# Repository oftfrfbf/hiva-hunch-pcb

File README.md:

# H.I.V.A Hunch PCB v2

The H.I.V.A Hunch PCB v2 is a medical device designed to monitor and restrict the presence of gas bubbles suspended in fluid passing through PVC tubing.

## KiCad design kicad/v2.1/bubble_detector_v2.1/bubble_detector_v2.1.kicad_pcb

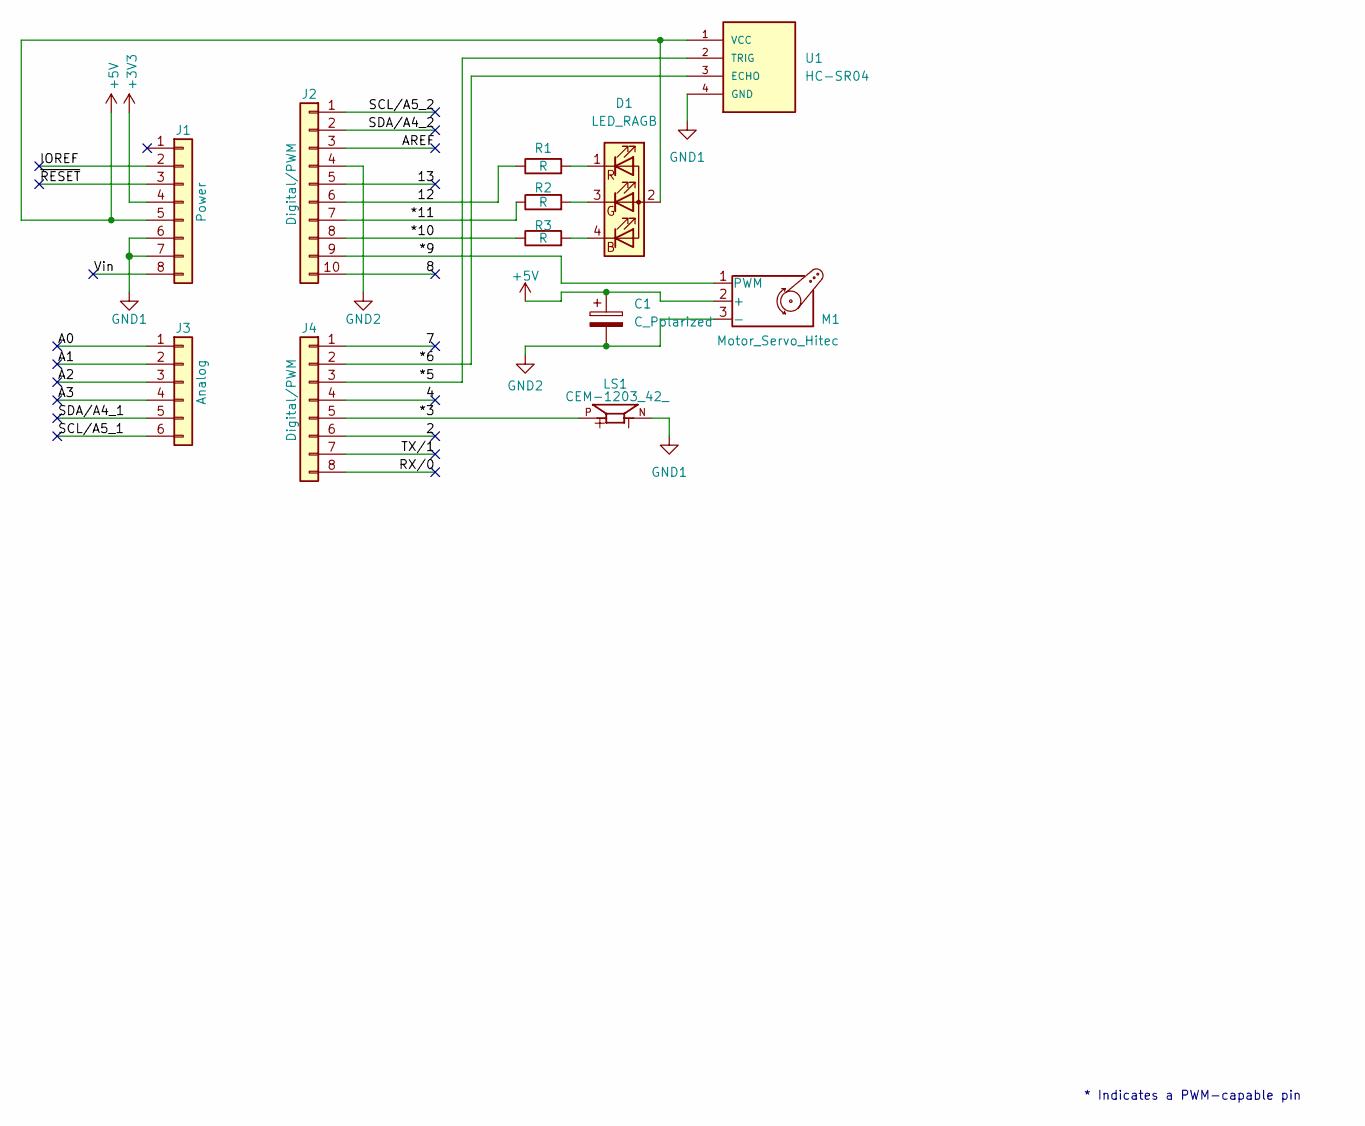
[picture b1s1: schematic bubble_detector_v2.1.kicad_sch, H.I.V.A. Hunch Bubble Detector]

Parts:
C1: C_Polarized; CP_Radial_D5.0mm_P2.50mm
D1: LED_RAGB; LED_D5.0mm-4_RGB
J1: Power; PinSocket_1x08_P2.54mm_Vertical
J2: Digital/PWM; PinSocket_1x10_P2.54mm_Vertical
J3: Analog; PinSocket_1x06_P2.54mm_Vertical
J4: Digital/PWM; PinSocket_1x08_P2.54mm_Vertical
LS1: CEM-1203_42_
M1: Motor_Servo_Hitec; PinHeader_1x03_P2.54mm_Vertical
R1, R2, R3: R; R_Axial_DIN0309_L9.0mm_D3.2mm_P12.70mm_Horizontal
U1: HC-SR04; XCVR_HC-SR04

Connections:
+3V3: J1.4
+5V: C1.1, D1.2 (A), J1.5, M1.2 (+), U1.1 (VCC)
/2: J4.6
/4: J4.4
/7: J4.1
/8: J2.10
/12: J2.6, R1.1
/13: J2.5
/*3: J4.5, LS1.P
/*5: J4.3, U1.2 (TRIG)
/*6: J4.2, U1.3 (ECHO)
/*9: J2.9, M1.1 (PWM)
/*10: J2.8, R3.1
/*11: J2.7, R2.1
/A0: J3.1
/A1: J3.2
/A2: J3.3
/A3: J3.4
/AREF: J2.3
/IOREF: J1.2
/RX/0: J4.8
/SCL/A5_1: J3.6
/SCL/A5_2: J2.1
/SDA/A4_1: J3.5
/SDA/A4_2: J2.2
/TX/1: J4.7
/Vin: J1.8
/~RESET: J1.3
GND1: J1.6, J1.7, LS1.N, U1.4 (GND)
GND2: C1.2, J2.4, M1.3 (-)
unnamed: D1.4 (BK), R3.2
unnamed: D1.3 (GK), R2.2
unnamed: D1.1 (RK), R1.2

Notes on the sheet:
* Indicates a PWM-capable pin

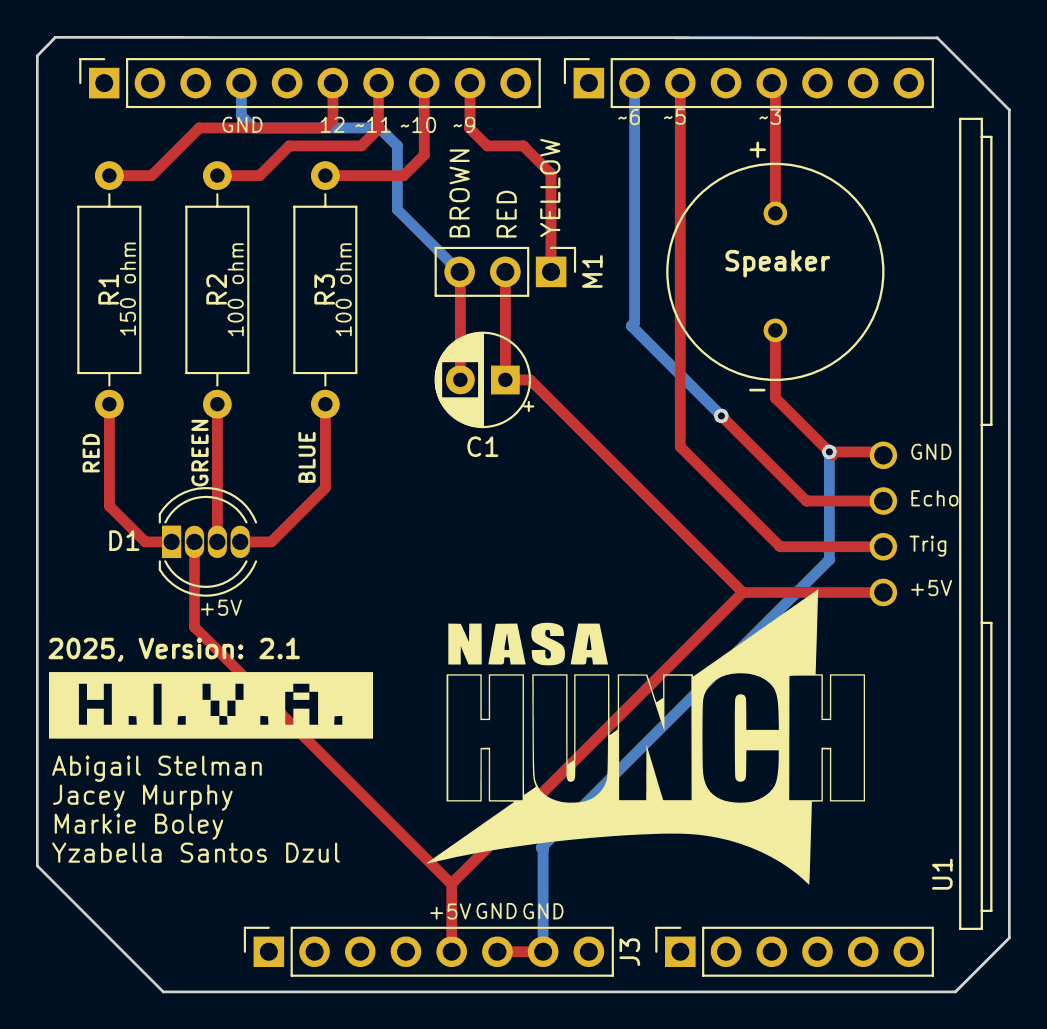
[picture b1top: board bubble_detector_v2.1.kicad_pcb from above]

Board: 2 copper layers, 54.0 x 53.0 mm, 12 parts (0 on the bottom side), 13 nets.

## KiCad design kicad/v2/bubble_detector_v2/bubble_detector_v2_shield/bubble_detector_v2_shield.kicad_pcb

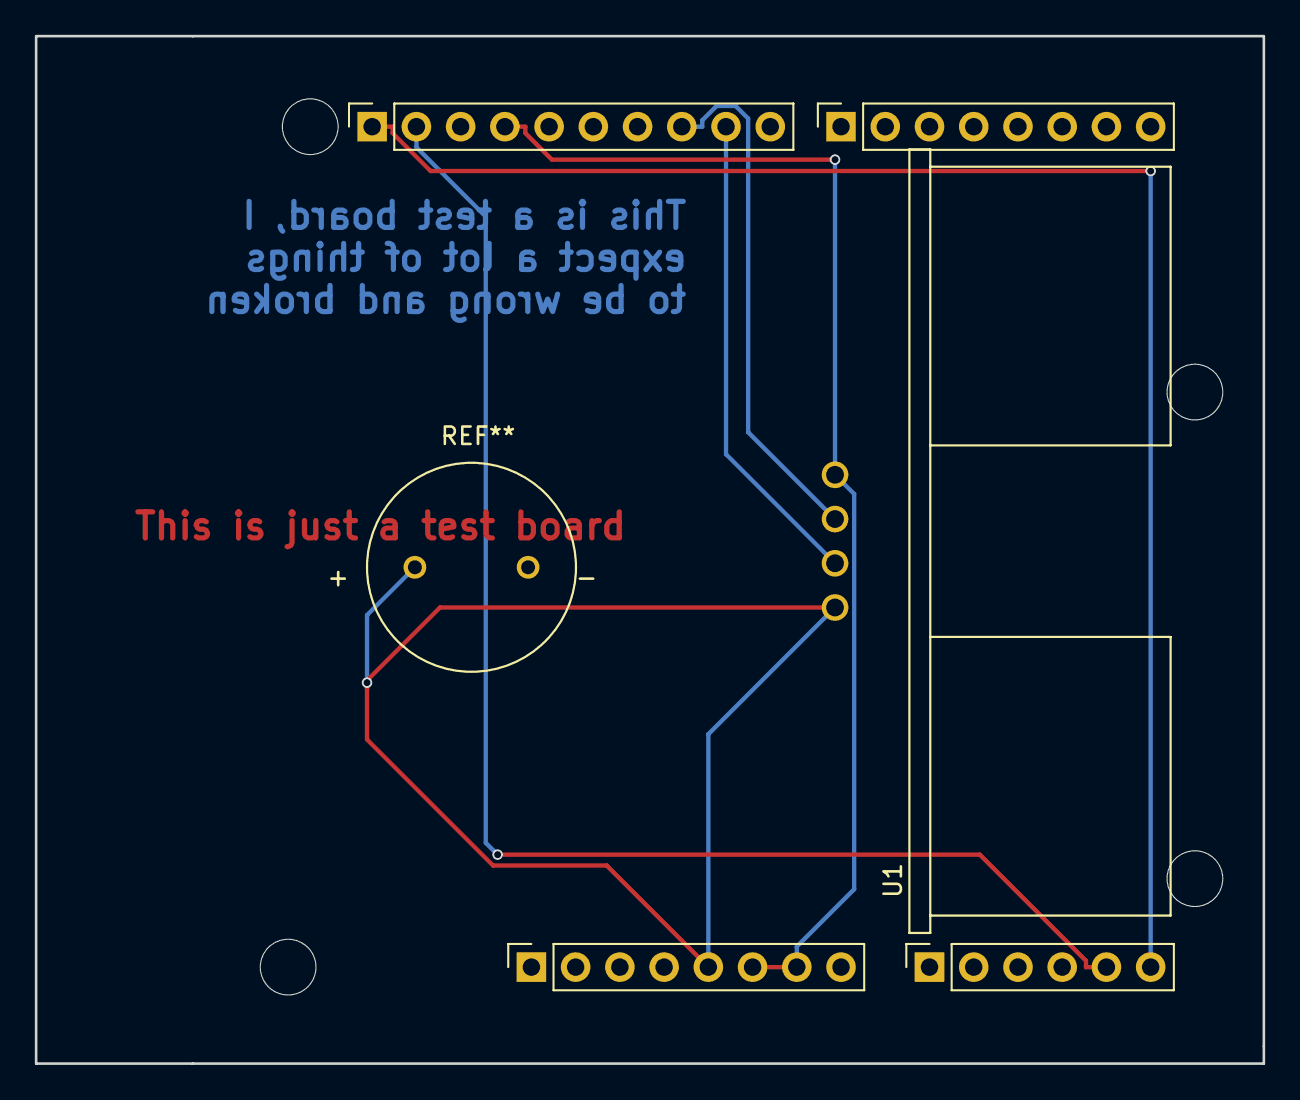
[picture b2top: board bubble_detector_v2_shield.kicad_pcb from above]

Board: 2 copper layers, 70.5 x 59.0 mm, 9 parts (0 on the bottom side), 5 nets.

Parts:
J1: Power; PinSocket_1x08_P2.54mm_Vertical
J2: Digital/PWM; PinSocket_1x10_P2.54mm_Vertical
J3: Analog; PinSocket_1x06_P2.54mm_Vertical
J4: Digital/PWM; PinSocket_1x08_P2.54mm_Vertical
MH1, MH2, MH3, MH4: MountingHole_3.2mm
U1: HC-SR04; XCVR_HC-SR04

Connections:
/*9: J2.9, U1.2 (TRIG)
/*10: J2.8, U1.3 (ECHO)
/SCL/A5: J2.1, J3.6
/SDA/A4: J2.2, J3.5
GND: J1.6, J1.7, J2.4, U1.4 (GND)

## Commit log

2025-02-12 added initial files
2025-02-12 added arduino sketch
2025-02-12 added v1.1 gerber files
2025-02-15 added the hc-sr04 to the board
2025-02-15 missing edge cut
2025-02-26 have sensor and buzzer and led added to board
2025-03-01 Update hiva-hunch.ino
    all pins specified to correct positions
2025-03-01 adding arduino library
2025-03-02 added servo and am working on schematic
2025-03-02 Added all componenets, generated gerbers
2025-03-02 added gerber v1.1 files back to project
2025-03-04 finished design review w team, adding last touches
2025-03-04 continuted adding last touches
2025-03-04 added osh park order pdf
